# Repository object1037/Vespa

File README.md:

# Vespa

**[[BOOTHで販売中！]](https://pentronic-lab.booth.pm/items/7670599)**

The Vespa is a 50% wireless keyboard with an ortholinear layout.

- 52 keys
- MX/Choc hotswap
- Bluetooth and USB-C connectivity
- AA battery powered
- ZMK firmware with ZMK Studio support

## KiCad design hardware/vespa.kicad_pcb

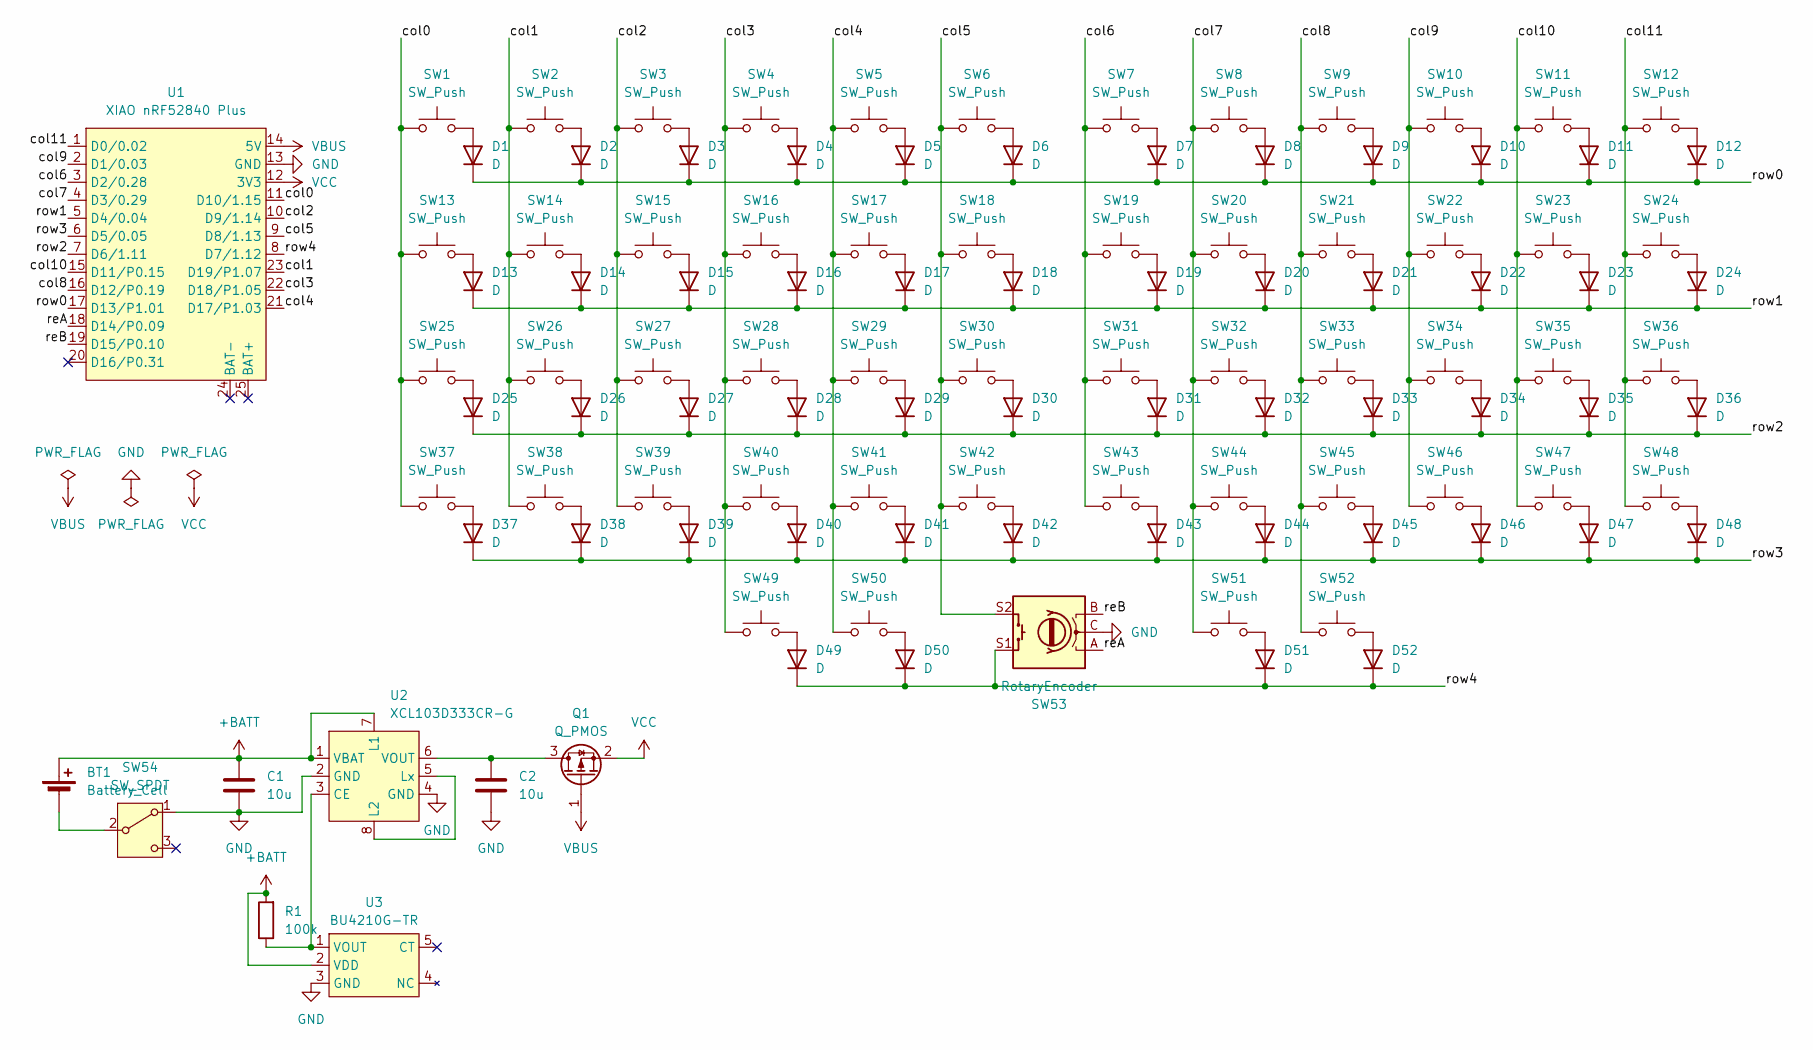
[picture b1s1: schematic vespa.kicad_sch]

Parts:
BT1: Battery_Cell; BatteryHolder_Keystone_2460_1xAA
C1, C2: 10u; C_0603_1608Metric_Pad1.08x0.95mm_HandSolder
D1, D2, D3, D4, D5, D6, D7, D8, D9, D10, D11, D12, D13, D14, D15, D16, D17, D18, D19, D20, D21, D22, D23, D24, D25, D26, D27, D28, D29, D30, D31, D32, D33, D34, D35, D36, D37, D38, D39, D40, D41, D42, D43, D44, D45, D46, D47, D48, D49, D50, D51, D52: D; D_SOD-323_HandSoldering
Q1: Q_PMOS; SOT-23-3
R1: 100k; R_0603_1608Metric_Pad0.98x0.95mm_HandSolder
SW1, SW2, SW3, SW4, SW5, SW6, SW7, SW8, SW9, SW10, SW11, SW12, SW13, SW14, SW15, SW16, SW17, SW18, SW19, SW20, SW21, SW22, SW23, SW24, SW25, SW26, SW27, SW28, SW29, SW30, SW31, SW32, SW33, SW34, SW35, SW36, SW37, SW38, SW39, SW40, SW41, SW42, SW43, SW44, SW45, SW46, SW47, SW48, SW49, SW50, SW51, SW52: SW_Push; MX_Choc_v1v2_Hotswap_1u
SW53: RotaryEncoder; re111f
SW54: SW_SPDT; SW_SPDT_IS-1245T
U1: XIAO nRF52840 Plus; XIAO-nRF52840-Plus-SMD
U2: XCL103D333CR-G; CL2025-02
U3: BU4210G-TR; SSOP5

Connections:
+BATT: BT1.1 (+), C1.1, R1.2, U2.1 (VBAT), U2.7 (L1), U3.2 (VDD); also elsewhere on the board
/col0: SW1.1, SW13.1, SW25.1, SW37.1, U1.11 (D10/1.15)
/col1: SW2.1, SW14.1, SW26.1, SW38.1, U1.23 (D19/P1.07)
/col2: SW3.1, SW15.1, SW27.1, SW39.1, U1.10 (D9/1.14)
/col3: SW4.1, SW16.1, SW28.1, SW40.1, SW49.1, U1.22 (D18/P1.05)
/col4: SW5.1, SW17.1, SW29.1, SW41.1, SW50.1, U1.21 (D17/P1.03)
/col5: SW6.1, SW18.1, SW30.1, SW42.1, SW53.S2, U1.9 (D8/1.13)
/col6: SW7.1, SW19.1, SW31.1, SW43.1, U1.3 (D2/0.28)
/col7: SW8.1, SW20.1, SW32.1, SW44.1, SW51.1, U1.4 (D3/0.29)
/col8: SW9.1, SW21.1, SW33.1, SW45.1, SW52.1, U1.16 (D12/P0.19)
/col9: SW10.1, SW22.1, SW34.1, SW46.1, U1.2 (D1/0.03)
/col10: SW11.1, SW23.1, SW35.1, SW47.1, U1.15 (D11/P0.15)
/col11: SW12.1, SW24.1, SW36.1, SW48.1, U1.1 (D0/0.02)
/reA: SW53.A, U1.18 (D14/P0.09)
/reB: SW53.B, U1.19 (D15/P0.10)
/row0: D1.1 (K), D2.1 (K), D3.1 (K), D4.1 (K), D5.1 (K), D6.1 (K), D7.1 (K), D8.1 (K), D9.1 (K), D10.1 (K), D11.1 (K), D12.1 (K), U1.17 (D13/P1.01)
/row1: D13.1 (K), D14.1 (K), D15.1 (K), D16.1 (K), D17.1 (K), D18.1 (K), D19.1 (K), D20.1 (K), D21.1 (K), D22.1 (K), D23.1 (K), D24.1 (K), U1.5 (D4/0.04)
/row2: D25.1 (K), D26.1 (K), D27.1 (K), D28.1 (K), D29.1 (K), D30.1 (K), D31.1 (K), D32.1 (K), D33.1 (K), D34.1 (K), D35.1 (K), D36.1 (K), U1.7 (D6/1.11)
/row3: D37.1 (K), D38.1 (K), D39.1 (K), D40.1 (K), D41.1 (K), D42.1 (K), D43.1 (K), D44.1 (K), D45.1 (K), D46.1 (K), D47.1 (K), D48.1 (K), U1.6 (D5/0.05)
/row4: D49.1 (K), D50.1 (K), D51.1 (K), D52.1 (K), SW53.S1, U1.8 (D7/1.12)
GND: C1.2, C2.2, SW53.C, SW54.1 (A), U1.13 (GND), U2.2 (GND), U2.4 (GND), U3.3 (GND)
unnamed 21: BT1.2 (-), SW54.2 (B); also elsewhere on the board
unnamed: D1.2 (A), SW1.2
unnamed: D2.2 (A), SW2.2
unnamed: D3.2 (A), SW3.2
unnamed: D4.2 (A), SW4.2
unnamed: D5.2 (A), SW5.2
unnamed: D6.2 (A), SW6.2
unnamed: D7.2 (A), SW7.2
unnamed: D8.2 (A), SW8.2
unnamed: D9.2 (A), SW9.2
unnamed: D10.2 (A), SW10.2
unnamed: D11.2 (A), SW11.2
unnamed: D12.2 (A), SW12.2
unnamed: D13.2 (A), SW13.2
unnamed: D14.2 (A), SW14.2
unnamed: D15.2 (A), SW15.2
unnamed: D16.2 (A), SW16.2
unnamed: D17.2 (A), SW17.2
unnamed: D18.2 (A), SW18.2
unnamed: D19.2 (A), SW19.2
unnamed: D20.2 (A), SW20.2
unnamed: D21.2 (A), SW21.2
unnamed: D22.2 (A), SW22.2
unnamed: D23.2 (A), SW23.2
unnamed: D24.2 (A), SW24.2
unnamed: D25.2 (A), SW25.2
unnamed: D26.2 (A), SW26.2
unnamed: D27.2 (A), SW27.2
unnamed: D28.2 (A), SW28.2
unnamed: D29.2 (A), SW29.2
unnamed: D30.2 (A), SW30.2
unnamed: D31.2 (A), SW31.2
unnamed: D32.2 (A), SW32.2
unnamed: D33.2 (A), SW33.2
unnamed: D34.2 (A), SW34.2
unnamed: D35.2 (A), SW35.2
unnamed: D36.2 (A), SW36.2
unnamed: D37.2 (A), SW37.2
unnamed: D38.2 (A), SW38.2
unnamed: D39.2 (A), SW39.2
unnamed: D40.2 (A), SW40.2
unnamed: D41.2 (A), SW41.2
unnamed: D42.2 (A), SW42.2
unnamed: D43.2 (A), SW43.2
unnamed: D44.2 (A), SW44.2
unnamed: D45.2 (A), SW45.2
unnamed: D46.2 (A), SW46.2
unnamed: D47.2 (A), SW47.2
unnamed: D48.2 (A), SW48.2
unnamed: D49.2 (A), SW49.2
unnamed: D50.2 (A), SW50.2
unnamed: D51.2 (A), SW51.2
unnamed: D52.2 (A), SW52.2
unnamed: C2.1, Q1.3 (D), U2.6 (VOUT)
unnamed: R1.1, U2.3 (CE), U3.1 (VOUT)
unnamed: U2.5 (Lx), U2.8 (L2)
VBUS: Q1.1 (G), U1.14 (5V)
VCC: Q1.2 (S), U1.12 (3V3)

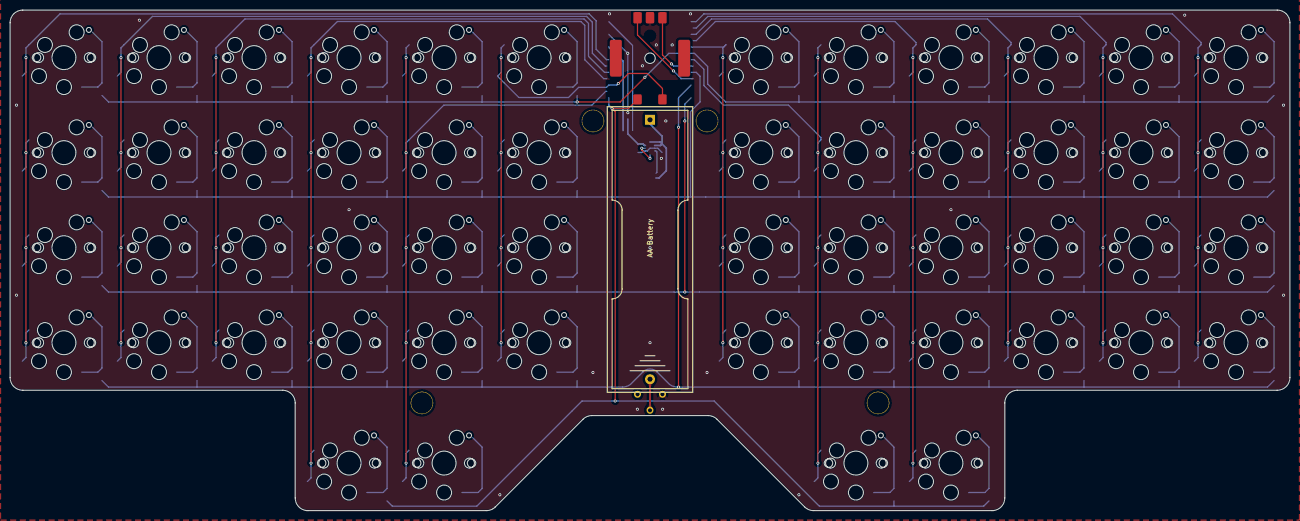
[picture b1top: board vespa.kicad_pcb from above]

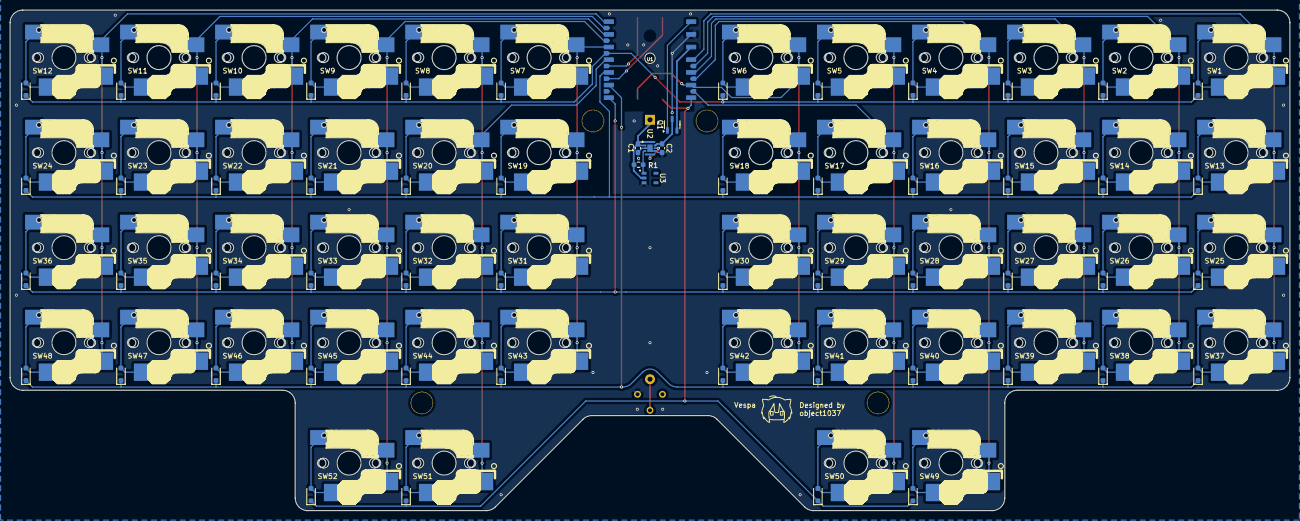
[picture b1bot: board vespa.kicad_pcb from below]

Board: 2 copper layers, 256.5 x 100.3 mm, 118 parts (112 on the bottom side), 79 nets.

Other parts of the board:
AA Battery: Battery_Cell; BatteryHolder_Keystone_2460_1xAA
Ref**: Val**; m2_Spacer_Hole
Ref**#2, Ref**#3, Ref**#4: Val**; m2_Spacer_Hole

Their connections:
+BATT: AA Battery.1 (+); also elsewhere on the board
unnamed 21: AA Battery.2 (-); also elsewhere on the board

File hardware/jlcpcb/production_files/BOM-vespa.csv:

Comment,Designator,Footprint,LCSC,Quantity
100k,R1,R_0603_1608Metric_Pad0.98x0.95mm_HandSolder,C25803,1
10u,"C1,C2",C_0603_1608Metric_Pad1.08x0.95mm_HandSolder,C19702,2
BU4210G-TR,U3,SSOP5,C2066584,1
D,"D1,D10,D11,D12,D13,D14,D15,D16,D17,D18,D19,D2,D20,D21,D22,D23,D24,D25,D26,D27,D28,D29,D3,D30,D31,D32,D33,D34,D35,D36,D37,D38,D39,D4,D40,D41,D42,D43,D44,D45,D46,D47,D48,D49,D5,D50,D51,D52,D6,D7,D8,D9",D_SOD-323_HandSoldering,C2128,52
Q_PMOS,Q1,SOT-23-3,C15127,1
SW_Push,"SW1,SW10,SW11,SW12,SW13,SW14,SW15,SW16,SW17,SW18,SW19,SW2,SW20,SW21,SW22,SW23,SW24,SW25,SW26,SW27,SW28,SW29,SW3,SW30,SW31,SW32,SW33,SW34,SW35,SW36,SW37,SW38,SW39,SW4,SW40,SW41,SW42,SW43,SW44,SW45,SW46,SW47,SW48,SW49,SW5,SW50,SW51,SW52,SW6,SW7,SW8,SW9",MX_Choc_v1v2_Hotswap_1u,C41430893,52
XCL103D333CR-G,U2,CL2025-02,C7158885,1

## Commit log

2025-10-21 basic schematic
2025-10-22 basic routing
2025-10-27 update pcb
2025-10-27 plate v1
2025-11-05 add case step file
2025-11-05 add logo to the case
2025-11-05 update ignore file
2025-11-05 add firmware as submodule
2025-11-05 add README
2025-11-05 update readme with keymap
2025-11-05 update firmware
2025-11-06 add licenses
2025-11-07 add userguide
2025-11-12 update dc-dc input routing
2025-11-12 remove docs from this repo
2025-11-15 update firmware submod
2025-11-16 move case data to dedicated dir
2025-11-29 update README with image
